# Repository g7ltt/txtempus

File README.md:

# txtempus

DCF77/MSF/WWVB/JJY format short range time transmitter for the RPi Zero. Enables the setting of wristwatches with time receivers in them.

This is an antenna "hat" board for the RPi-Zero but it should also fit other RPI's too 

https://github.com/hzeller/txtempus for more info on the RPi aspect.

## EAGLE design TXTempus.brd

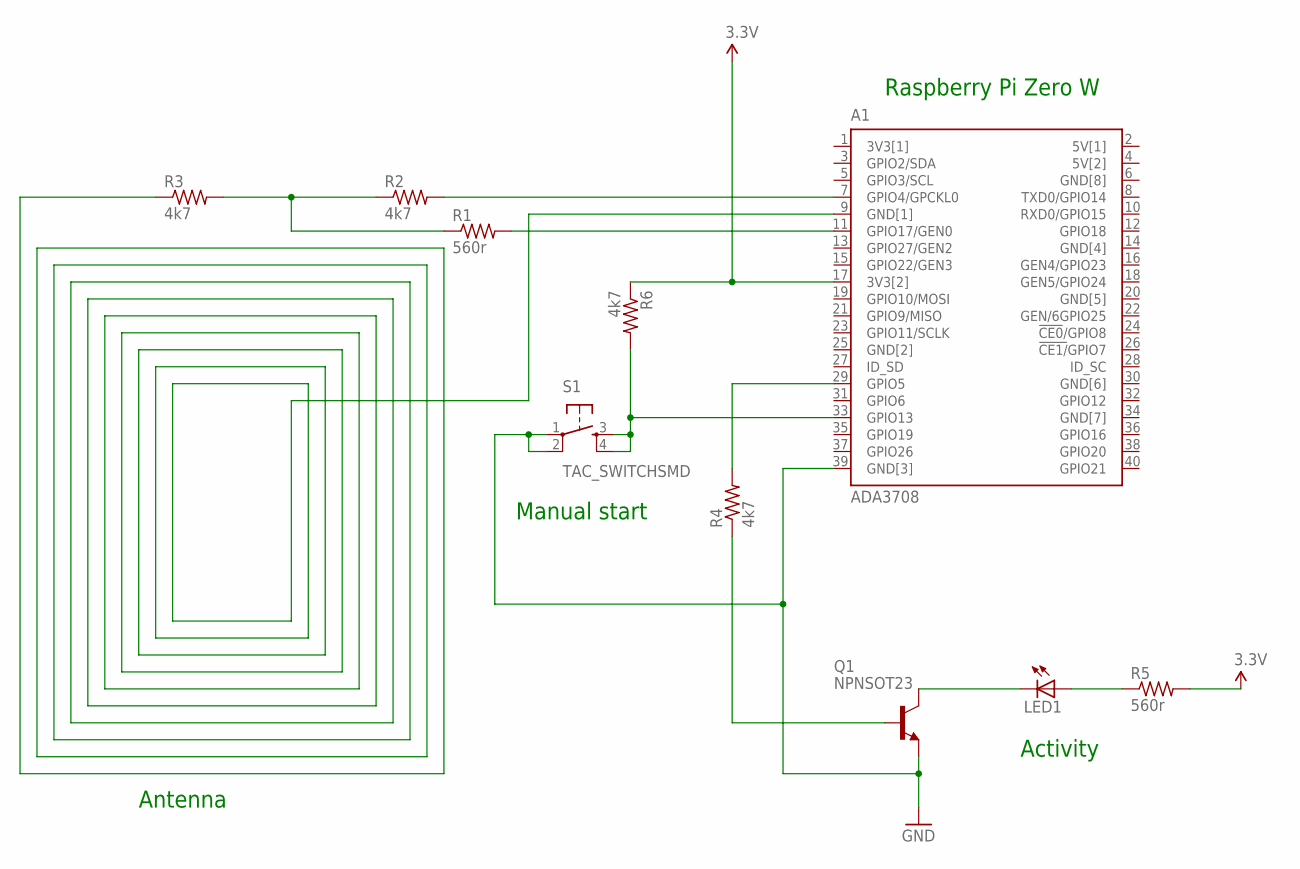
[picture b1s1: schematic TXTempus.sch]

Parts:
A1: ADA3708; ADA3708_RPI-ZERO
LED1: LED_E; LED_1206
Q1: NPNSOT23; SOT23
R1, R5: 560r; M0805
R2, R3, R4, R6: 4k7; M0805
S1: TAC_SWITCHSMD; TACTILE-SWITCH-SMD

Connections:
3.3V: A1.17 (3V3[2]), R5.2, R6.1
3V3[1]: A1.1 (3V3[1])
5V[1]: A1.2 (5V[1])
5V[2]: A1.4 (5V[2])
GND: A1.39 (GND[3]), Q1.2 (E), S1.1, S1.2
GND[2]: A1.25 (GND[2])
GND[4]: A1.14 (GND[4])
GND[5]: A1.20 (GND[5])
GND[6]: A1.30 (GND[6])
GND[7]: A1.34 (GND[7])
GND[8]: A1.6 (GND[8])
unnamed: A1.11 (GPIO17/GEN0), R1.2
unnamed: A1.7 (GPIO4/GPCKL0), R2.2
unnamed: R1.1, R2.1, R3.2
unnamed: A1.9 (GND[1]), R3.1
unnamed: A1.29 (GPIO5), R4.2
unnamed: Q1.1 (B), R4.1
unnamed: LED1.C, Q1.3 (C)
unnamed: LED1.A, R5.1
unnamed: A1.33 (GPIO13), R6.2, S1.3, S1.4

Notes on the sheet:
Raspberry Pi Zero W
Manual start
Antenna
Activity

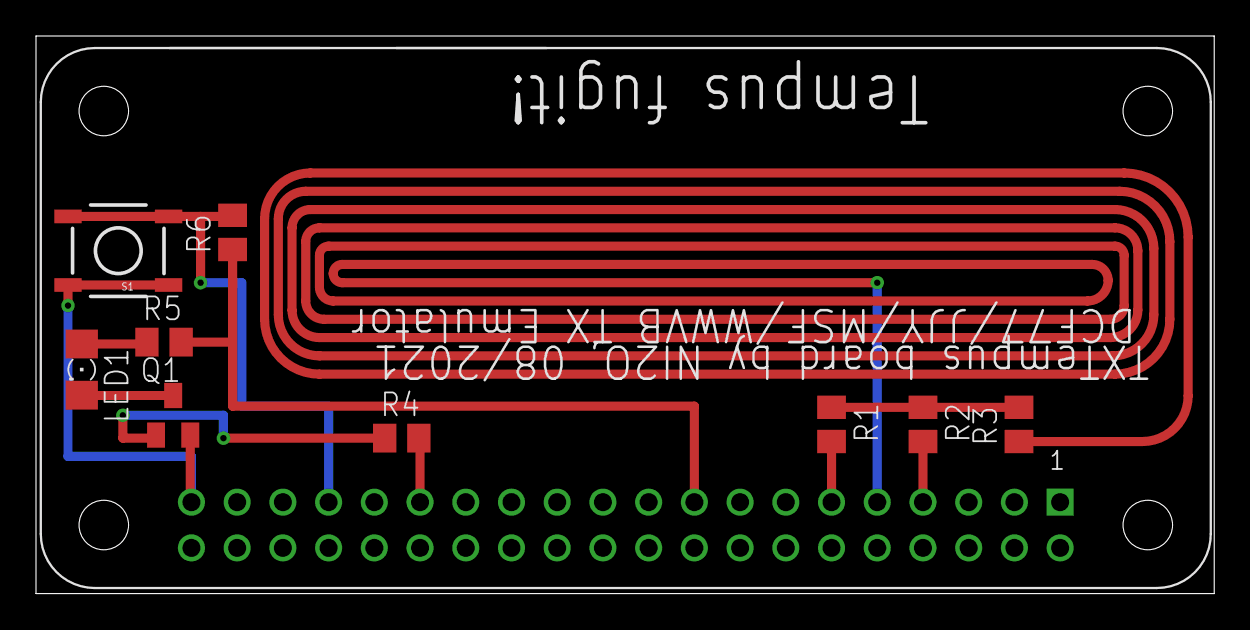
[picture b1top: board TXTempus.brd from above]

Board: 2 copper layers, 65.5 x 31.0 mm, 10 parts (0 on the bottom side), 11 nets.

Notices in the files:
parts and their libraries:
SparkFun-Retired: Licensing:Creative Commons ShareAlike 4.0 International - https://creativecommons.org/licenses/by-sa/4.0
SparkFun: Licensing: CC v3.0 Share-Alike You are welcome to use this library for commercial purposes.
